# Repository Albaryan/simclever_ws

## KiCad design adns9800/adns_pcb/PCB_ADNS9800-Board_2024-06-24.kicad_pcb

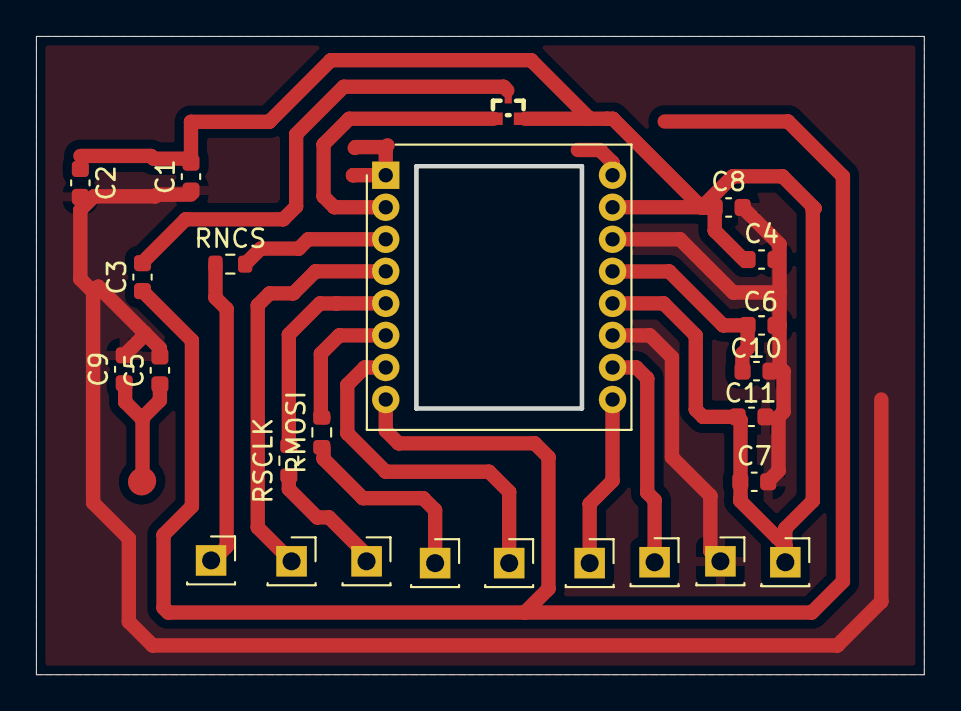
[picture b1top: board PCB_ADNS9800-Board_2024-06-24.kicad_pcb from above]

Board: 2 copper layers, 49.1 x 35.3 mm, 16 parts (0 on the bottom side), 10 nets.

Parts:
C1: 10nF; C_0603_1608Metric
C2: 1uF; C_0603_1608Metric
C3: 470pF; C_0603_1608Metric
C4, C5, C6, C7: 100nF; C_0603_1608Metric
C8: 3.3uF; C_0603_1608Metric
C9: 4.7uF; C_0603_1608Metric
C10, C11: 10uF; C_0603_1608Metric
RMOSI: 330; R_0603_1608Metric
RNCS: 330; R_0603_1608Metric
RSCLK: 330; R_0603_1608Metric
T1: NTA4151PT1G; SOT-416_L1.6-W0.8-P1.00-LS1.6-BR
U1: ADNS-9800_CP; ADNS-9800

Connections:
GND: C1.1, C2.2, C4.2, C5.2, C6.2, C7.2, C8.2, C9.2, C10.2, C11.2, U1.11, U1.14
MOSI: RMOSI.2, U1.6
NCS: RNCS.2, U1.3
SCLK: RSCLK.2, U1.5
U1_1: C3.2, T1.3, U1.1
U1_2: T1.1, U1.2
U1_8: C3.1, U1.8, U1.16
U1_13: C6.1, C10.1, U1.13
VCC: C5.1, C9.1, U1.9
VDD2: C1.2, C2.1, C4.1, C7.1, C8.1, C11.1, T1.2, U1.12, U1.15

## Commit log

2024-07-10 update repo
